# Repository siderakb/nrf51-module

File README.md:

# nRF51 Module

nRF51822 Bluetooth Low Energy module, used to replace [Adafruit Bluefruit LE SPI Friend](https://www.adafruit.com/product/2633) and [Raytac MDBT40-256RV3](https://www.raytac.com/product/ins.php?index_id=74).

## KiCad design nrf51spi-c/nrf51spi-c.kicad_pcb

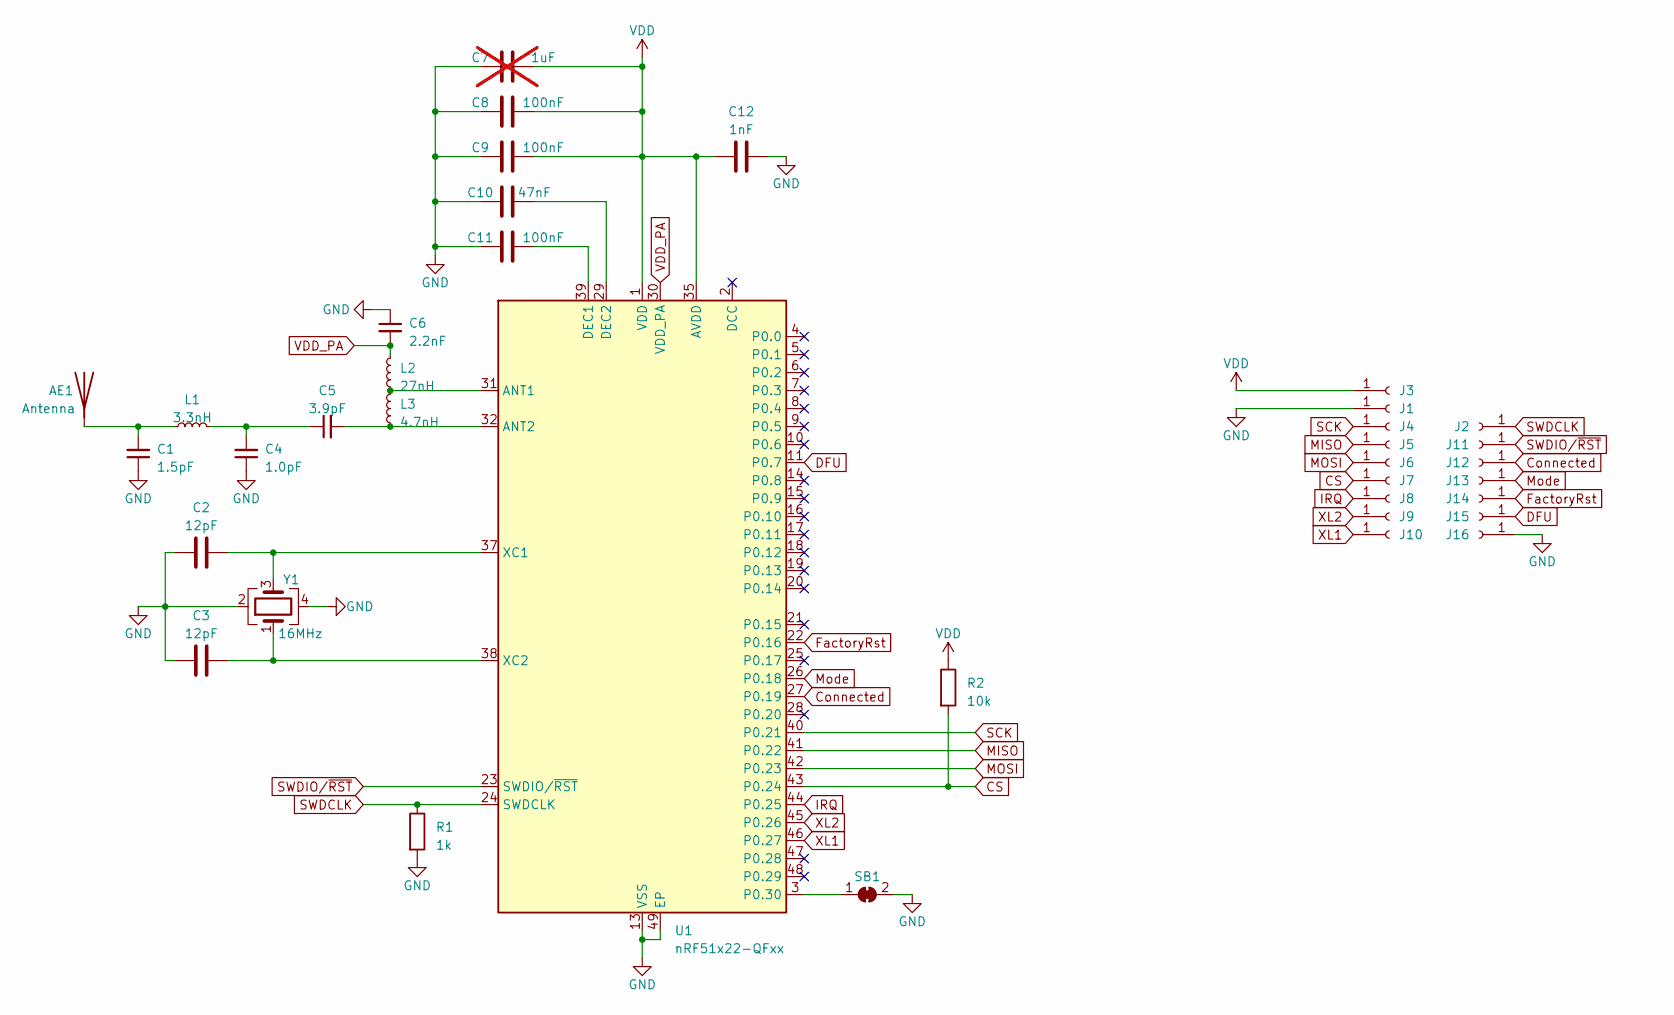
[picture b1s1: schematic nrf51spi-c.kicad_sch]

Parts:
AE1: Antenna; AN2051-245
C1: 1.5pF; C_0402_1005Metric
C2, C3: 12pF; C_0402_1005Metric
C4: 1.0pF; C_0402_1005Metric
C5: 3.9pF; C_0402_1005Metric
C6: 2.2nF; C_0402_1005Metric
C7: 1uF; C_0402_1005Metric; not fitted
C8, C9, C11: 100nF; C_0402_1005Metric
C10: 47nF; C_0402_1005Metric
C12: 1nF; C_0402_1005Metric
J1, J2, J3, J4, J5, J6, J7, J8, J9, J10, J11, J12, J13, J14, J15, J16: Conn_01x01_Socket; castellated_holes_1.27mm
L1: 3.3nH; L_0402_1005Metric
L2: 27nH; L_0402_1005Metric
L3: 4.7nH; L_0402_1005Metric
R1: 1k; R_0402_1005Metric
R2: 10k; R_0402_1005Metric
SB1: SolderJumper_2_Bridged; SolderJumper-2_P1.3mm_Bridged_RoundedPad1.0x1.5mm
U1: nRF51x22-QFxx; QFN-48-1EP_6x6mm_P0.4mm_EP4.6x4.6mm
Y1: 16MHz; Crystal_SMD_3225-4Pin_3.2x2.5mm

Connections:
CS: J7.1, R2.2, U1.43 (P0.24)
Connected: J12.1, U1.27 (P0.19)
DFU: J15.1, U1.11 (P0.7)
FactoryRst: J14.1, U1.22 (P0.16)
GND: C1.1, C2.1, C3.2, C4.1, C6.1, C7.1, C8.1, C9.1, C10.1, C11.1, C12.2, J1.1, J16.1, R1.2, SB1.2 (B), U1.13 (VSS), U1.33 (VSS), U1.34 (VSS), U1.49 (EP), Y1.2, Y1.4
IRQ: J8.1, U1.44 (P0.25)
MISO: J5.1, U1.41 (P0.22)
MOSI: J6.1, U1.42 (P0.23)
Mode: J13.1, U1.26 (P0.18)
unnamed: AE1.1 (A), C1.2, L1.1
unnamed: C4.2, C5.1, L1.2
unnamed: SB1.1 (A), U1.3 (P0.30)
unnamed: L2.1, L3.2, U1.31 (ANT1)
unnamed: C5.2, L3.1, U1.32 (ANT2)
unnamed: C11.2, U1.39 (DEC1)
unnamed: C10.2, U1.29 (DEC2)
unnamed: C2.2, U1.37 (XC1), Y1.3
unnamed: C3.1, U1.38 (XC2), Y1.1
SCK: J4.1, U1.40 (P0.21)
SWDCLK: J2.1, R1.1, U1.24 (SWDCLK)
SWDIO/~RST: J11.1, U1.23 (SWDIO/~RST)
VDD: C7.2, C8.2, C9.2, C12.1, J3.1, R2.1, U1.1 (VDD), U1.12 (VDD), U1.35 (AVDD), U1.36 (AVDD)
VDD_PA: C6.2, L2.2, U1.30 (VDD_PA)
XL1: J10.1, U1.46 (P0.27)
XL2: J9.1, U1.45 (P0.26)

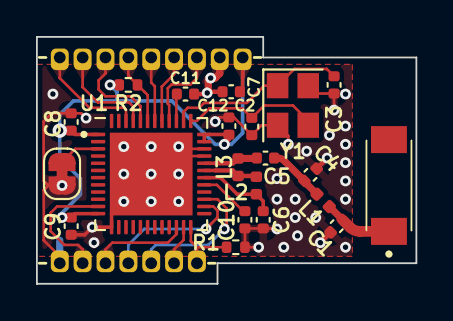
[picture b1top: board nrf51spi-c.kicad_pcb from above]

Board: 2 copper layers, 21.1 x 13.7 mm, 37 parts (0 on the bottom side), 25 nets.

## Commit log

2023-05-06 Init commit
2023-05-09 Add teradrops and castellated holes
2023-07-08 Create LICENSE
